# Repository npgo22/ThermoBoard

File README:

STATUS:
Initial decent layout and schematic are complete. PCB meets basic requirements.

TODO:
- Further review

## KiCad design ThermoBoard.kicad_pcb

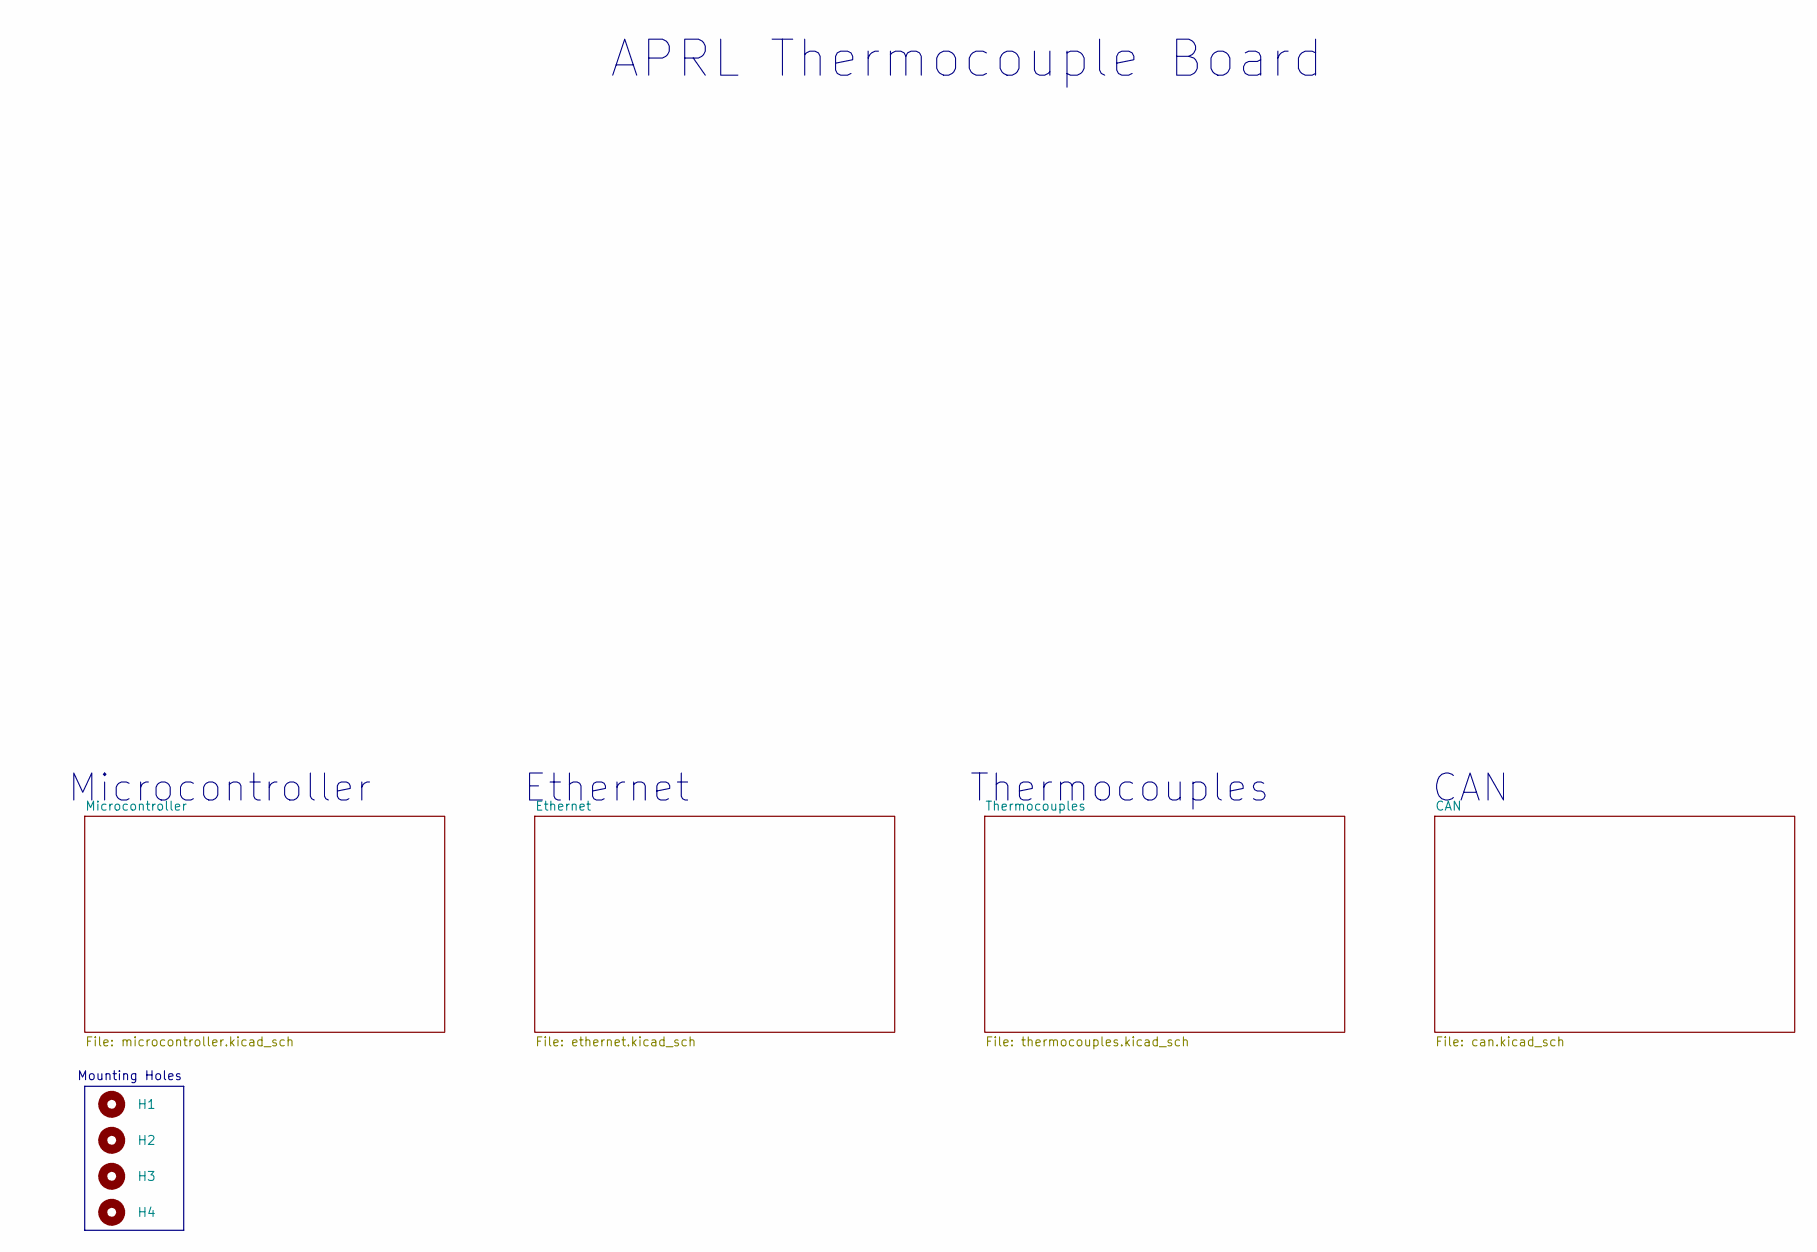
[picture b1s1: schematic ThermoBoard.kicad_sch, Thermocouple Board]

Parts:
H1, H2, H3, H4: MountingHole; MountingHole_3.2mm_M3

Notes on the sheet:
APRL Thermocouple Board
Mounting Holes
Thermocouples
Ethernet
Microcontroller
CAN

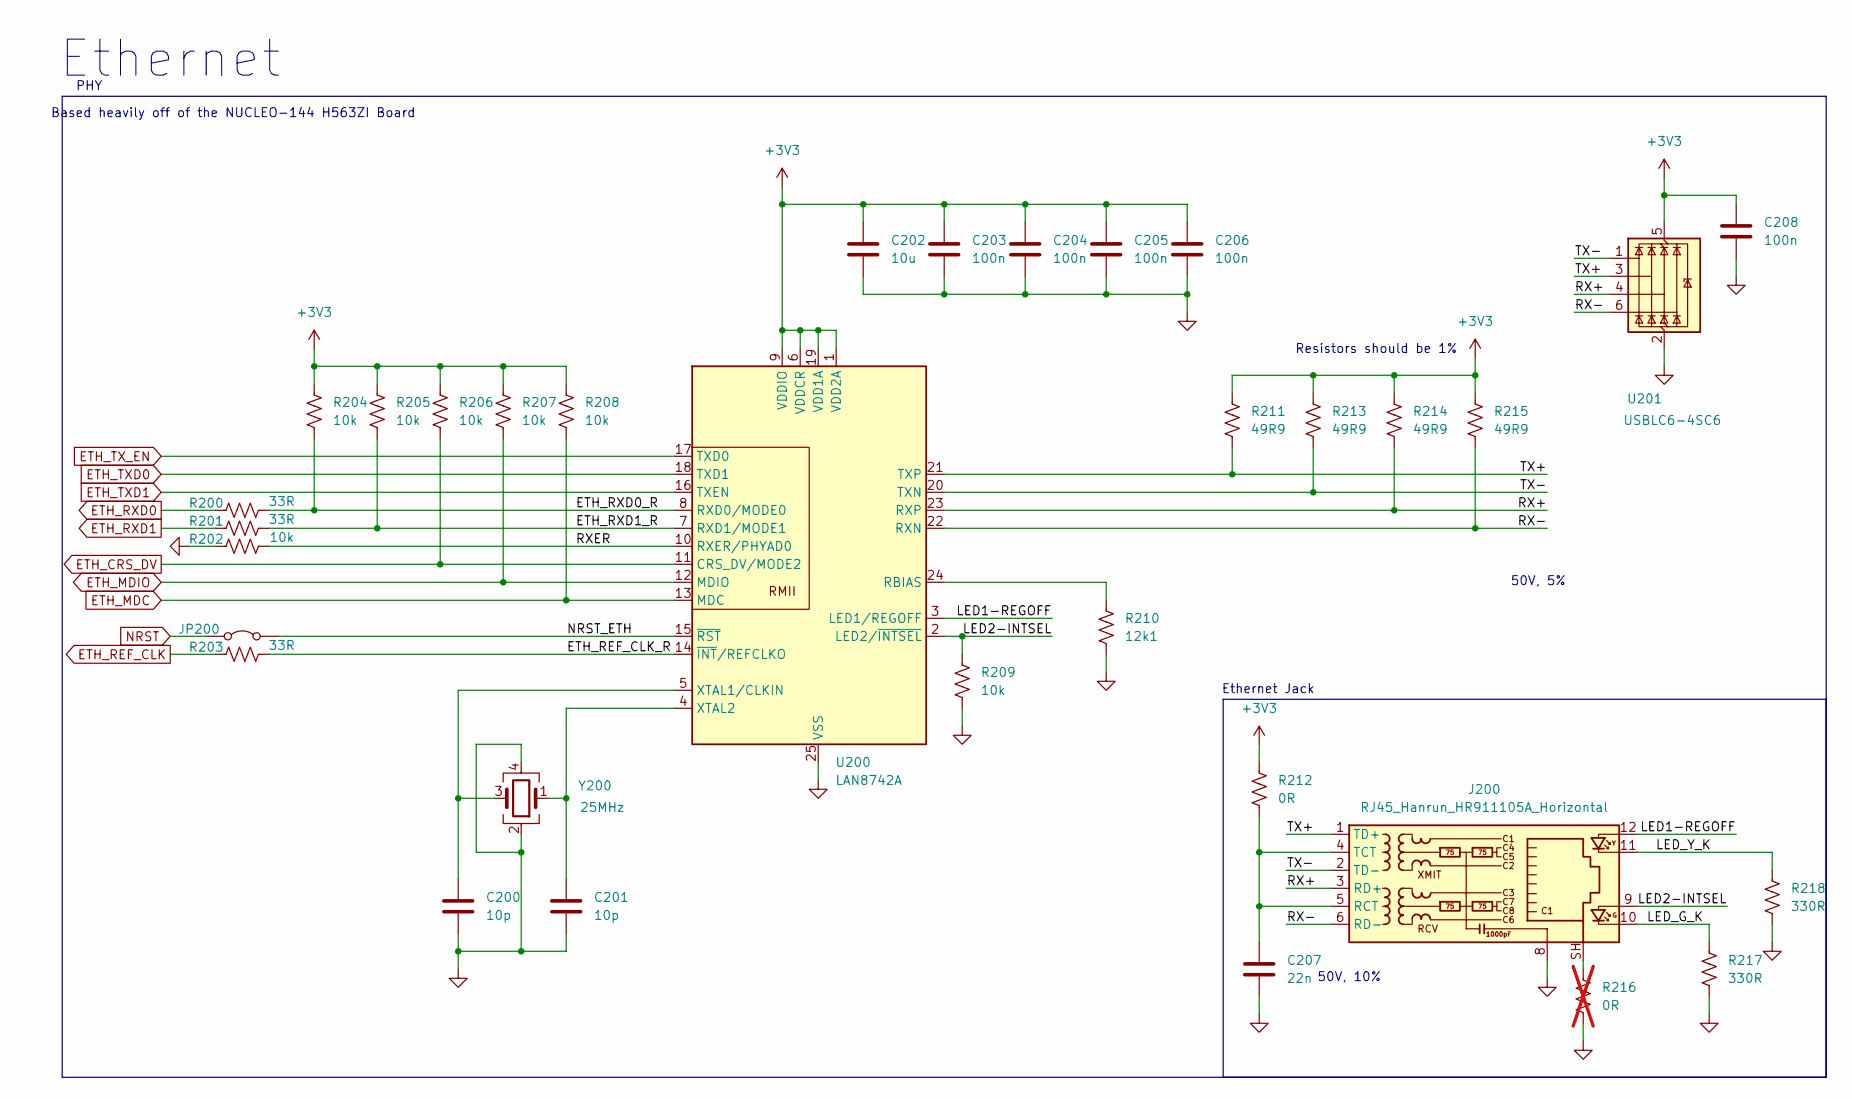
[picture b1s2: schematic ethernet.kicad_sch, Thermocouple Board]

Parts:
C200, C201: 10p; C_0402_1005Metric; LCSC C32949
C202: 10u; C_0603_1608Metric; LCSC C19702
C203, C204, C205, C206, C208: 100n; C_0402_1005Metric; LCSC C1525
C207: 22n; C_0402_1005Metric; LCSC C337699
J200: RJ45_Hanrun_HR911105A_Horizontal; LCSC C12074
JP200: Jumper_2_Bridged; SolderJumper-2_P1.3mm_Bridged_Pad1.0x1.5mm
R200, R201, R203: 33R; R_0402_1005Metric; LCSC C138002
R202, R204, R205, R206, R207, R208, R209: 10k; R_0402_1005Metric; LCSC C60490
R210: 12k1; R_0402_1005Metric; LCSC C25852
R211, R213, R214, R215: 49R9; R_0402_1005Metric; LCSC C87044
R212: 0R; R_0402_1005Metric; LCSC C106231
R216: 0R; R_0402_1005Metric; LCSC C106231; not fitted
R217, R218: 330R; R_0402_1005Metric; LCSC C105875
U200: LAN8742A; VQFN-24-1EP_4x4mm_P0.5mm_EP2.5x2.5mm_ThermalVias; LCSC C220794
U201: USBLC6-4SC6; SOT-23-6; LCSC C111212
Y200: 25MHz; CRYSTAL-SMD_4P-L2.0-W1.6-BL; LCSC C5765970

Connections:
+3V3: C202.1, C203.1, C204.1, C205.1, C206.1, C208.1, R204.1, R205.1, R206.1, R207.1, R208.1, R211.1, R212.1, R213.1, R214.1, R215.1, U200.1 (VDD2A), U200.6 (VDDCR), U200.9 (VDDIO), U200.19 (VDD1A), U201.5 (VBUS); also elsewhere on the board
/Ethernet/ETH_REF_CLK_R: R203.2, U200.14 (~INT/REFCLKO)
/Ethernet/ETH_RXD0_R: R200.2, R204.2, U200.8 (RXD0/MODE0)
/Ethernet/ETH_RXD1_R: R201.2, R205.2, U200.7 (RXD1/MODE1)
/Ethernet/LED1-REGOFF: J200.12, U200.3 (LED1/REGOFF)
/Ethernet/LED2-INTSEL: J200.9, R209.1, U200.2 (LED2/~INTSEL)
/Ethernet/LED_G_K: J200.10, R217.1
/Ethernet/LED_Y_K: J200.11, R218.1
/Ethernet/NRST_ETH: JP200.2 (B), U200.15 (~RST)
/Ethernet/RX+: J200.3 (RD+), R214.2, U200.23 (RXP), U201.4 (I/O3)
/Ethernet/RX-: J200.6 (RD-), R215.2, U200.22 (RXN), U201.6 (I/O4)
/Ethernet/RXER: R202.2, U200.10 (RXER/PHYAD0)
/Ethernet/TX+: J200.1 (TD+), R211.2, U200.21 (TXP), U201.3 (I/O2)
/Ethernet/TX-: J200.2 (TD-), R213.2, U200.20 (TXN), U201.1 (I/O1)
ETH_CRS_DV: R206.2, U200.11 (CRS_DV/MODE2); also elsewhere on the board
ETH_MDC: R208.2, U200.13 (MDC); also elsewhere on the board
ETH_MDIO: R207.2, U200.12 (MDIO); also elsewhere on the board
ETH_REF_CLK: R203.1; also elsewhere on the board
ETH_RXD0: R200.1; also elsewhere on the board
ETH_RXD1: R201.1; also elsewhere on the board
ETH_TXD0: U200.18 (TXD1); also elsewhere on the board
ETH_TXD1: U200.16 (TXEN); also elsewhere on the board
ETH_TX_EN: U200.17 (TXD0); also elsewhere on the board
GND: C200.2, C201.2, C202.2, C203.2, C204.2, C205.2, C206.2, C207.2, C208.2, J200.8, R202.1, R209.2, R210.2, R216.2, R217.2, R218.2, U200.25 (VSS), U201.2 (GND), Y200.2, Y200.4; also elsewhere on the board
NRST: JP200.1 (A); also elsewhere on the board
unnamed: J200.SH, R216.1
unnamed: C207.1, J200.4 (TCT), J200.5 (RCT), R212.2
unnamed: R210.1, U200.24 (RBIAS)
unnamed: C200.1, U200.5 (XTAL1/CLKIN), Y200.3
unnamed: C201.1, U200.4 (XTAL2), Y200.1

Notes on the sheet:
Based heavily off of the NUCLEO-144 H563ZI Board
Ethernet
Resistors should be 1%
Ethernet Jack
PHY
50V, 10%
50V, 5%

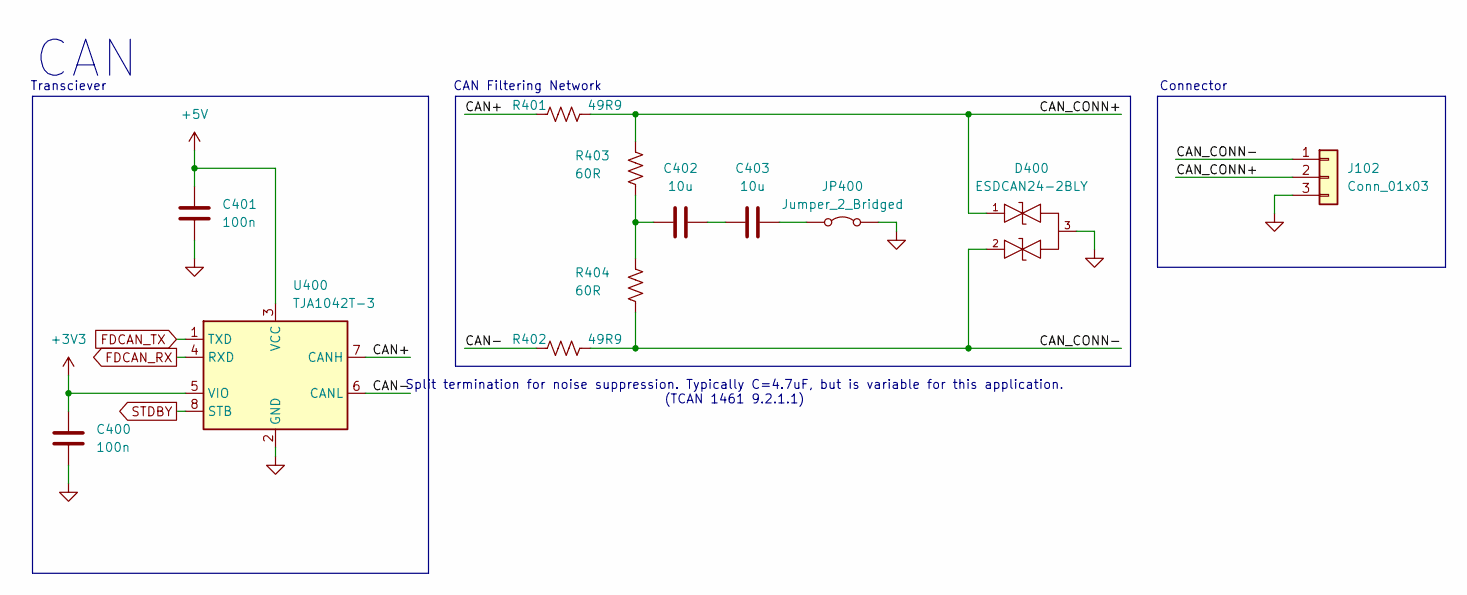
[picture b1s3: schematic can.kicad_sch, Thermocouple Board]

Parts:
C400, C401: 100n; C_0402_1005Metric; LCSC C1525
C402, C403: 10u; C_0603_1608Metric; LCSC C19702
D400: ESDCAN24-2BLY; SOT-23-3; LCSC C246766
J102: Conn_01x03; PinHeader_1x03_P2.54mm_Vertical; LCSC C2337
JP400: Jumper_2_Bridged; PinHeader_1x02_P2.54mm_Vertical; LCSC C2337
R401, R402: 49R9; R_0402_1005Metric; LCSC C87044
R403, R404: 60R; R_0402_1005Metric; LCSC C137954
U400: TJA1042T-3; SOIC-8_3.9x4.9mm_P1.27mm; LCSC C22445414

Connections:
+3V3: C400.1, U400.5 (VIO); also elsewhere on the board
+5V: C401.1, U400.3 (VCC); also elsewhere on the board
/CAN/CAN+: R401.1, U400.7 (CANH)
/CAN/CAN-: R402.1, U400.6 (CANL)
/CAN/CAN_CONN+: D400.1, J102.2, R401.2, R403.1
/CAN/CAN_CONN-: D400.2, J102.1, R402.2, R404.2
FDCAN_RX: U400.4 (RXD); also elsewhere on the board
FDCAN_TX: U400.1 (TXD); also elsewhere on the board
GND: C400.2, C401.2, D400.3, J102.3, JP400.2 (B), U400.2 (GND); also elsewhere on the board
unnamed: C402.1, R403.2, R404.1
unnamed: C402.2, C403.2
unnamed: C403.1, JP400.1 (A)
STDBY: U400.8 (STB); also elsewhere on the board

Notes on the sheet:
Split termination for noise suppression. Typically C=4.7uF, but is variable for this application. (TCAN 1461 9.2.1.1)
CAN
Transciever
CAN Filtering Network
Connector

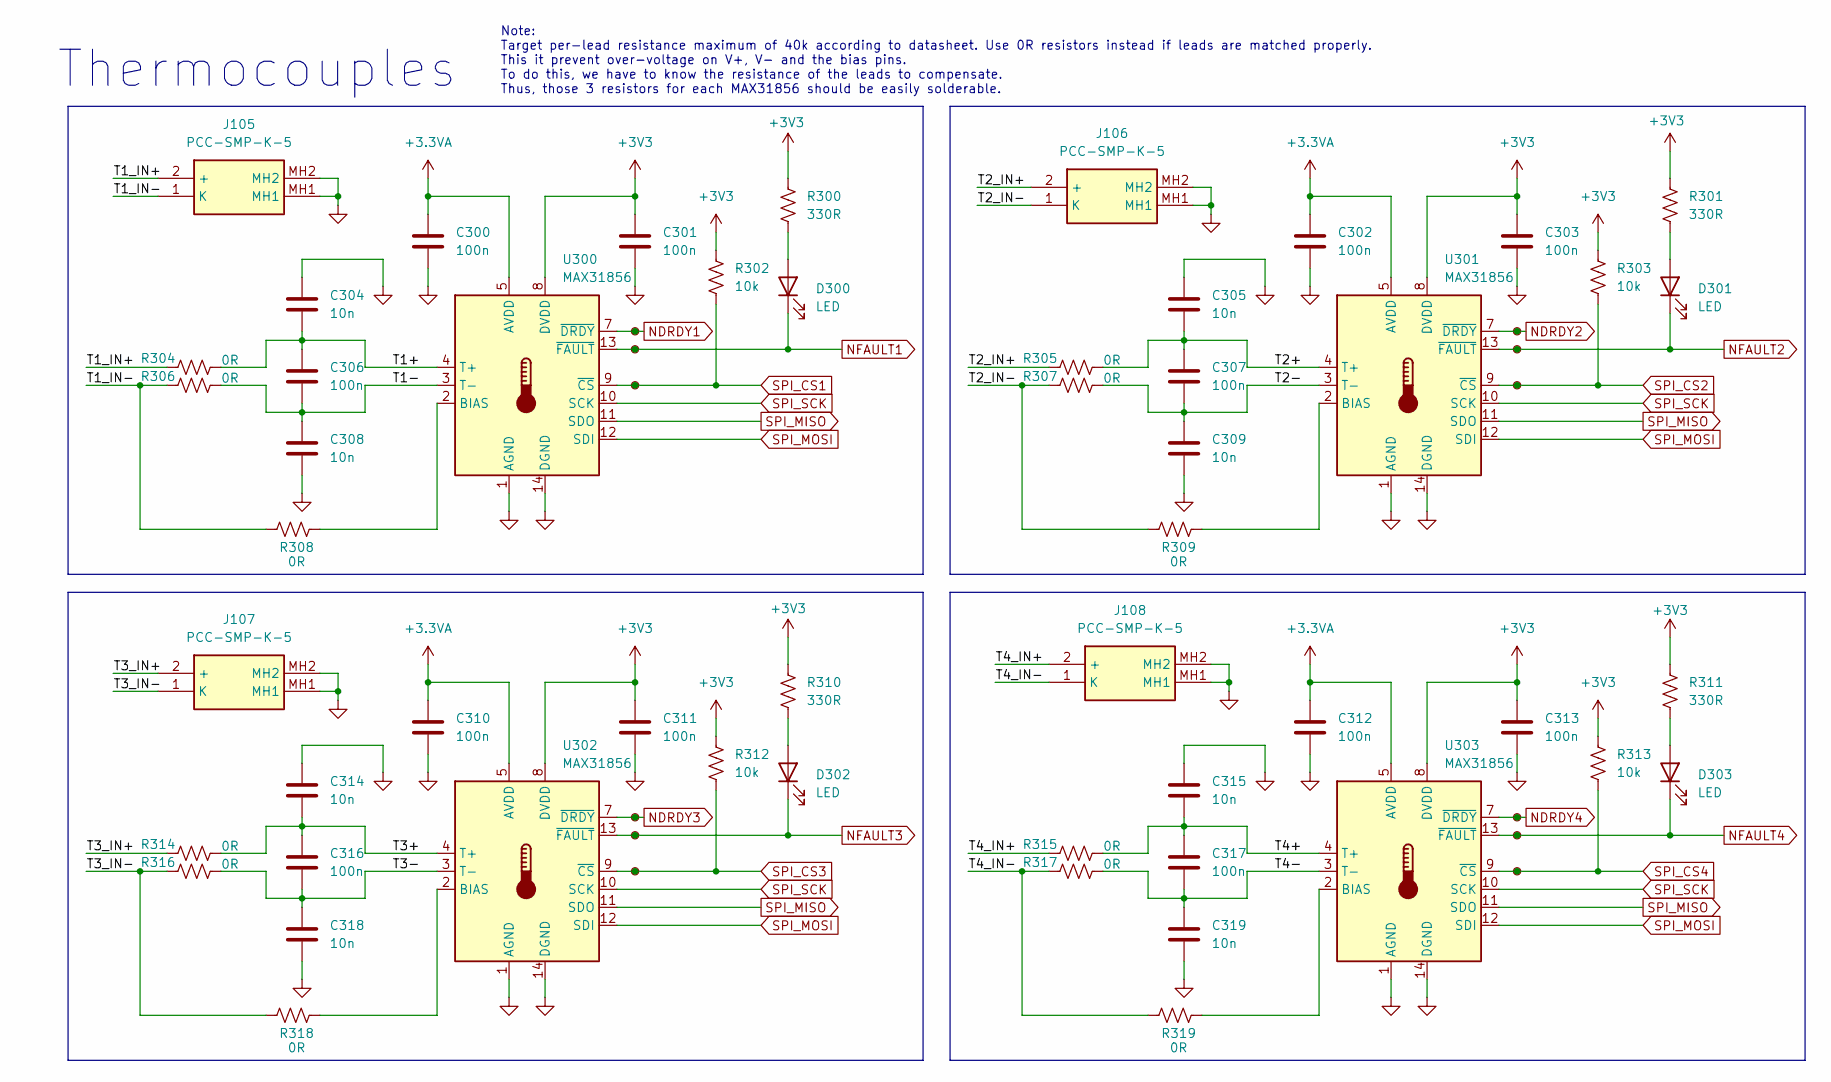
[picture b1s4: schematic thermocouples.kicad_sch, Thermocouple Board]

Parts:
C300, C301, C302, C303, C306, C307, C310, C311, C312, C313, C316, C317: 100n; C_0402_1005Metric; LCSC C1525
C304, C305, C308, C309, C314, C315, C318, C319: 10n; C_0402_1005Metric; LCSC C15195
D300, D301, D302, D303: LED; LED_0402_1005Metric; LCSC C965793
J105, J106, J107, J108: PCC-SMP-K-5; PCCSMPK5; Manufacturer_Part_Number PCC-SMP-K-5
R300, R301, R310, R311: 330R; R_0402_1005Metric; LCSC C105875
R302, R303, R312, R313: 10k; R_0402_1005Metric; LCSC C60490
R304, R305, R306, R307, R308, R309, R314, R315, R316, R317, R318, R319: 0R; R_0603_1608Metric; LCSC C95177
TP106, TP107, TP108, TP109, TP110, TP114, TP115, TP116, TP120, TP121, TP122, TP300: TestPoint_Small; TestPoint_Pad_D1.0mm
U300, U301, U302, U303: MAX31856; TSSOP-14_4.4x5mm_P0.65mm; LCSC C2653162

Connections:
+3.3VA: C300.1, C302.1, C310.1, C312.1, U300.5 (AVDD), U301.5 (AVDD), U302.5 (AVDD), U303.5 (AVDD); also elsewhere on the board
+3V3: C301.1, C303.1, C311.1, C313.1, R300.1, R301.1, R302.1, R303.1, R310.1, R311.1, R312.1, R313.1, U300.8 (DVDD), U301.8 (DVDD), U302.8 (DVDD), U303.8 (DVDD); also elsewhere on the board
/Thermocouples/T1+: C304.2, C306.1, R304.2, U300.4 (T+)
/Thermocouples/T1-: C306.2, C308.1, R306.2, U300.3 (T-)
/Thermocouples/T1_IN+: J105.2 (+), R304.1
/Thermocouples/T1_IN-: J105.1 (K), R306.1, R308.1
/Thermocouples/T2+: C305.2, C307.1, R305.2, U301.4 (T+)
/Thermocouples/T2-: C307.2, C309.1, R307.2, U301.3 (T-)
/Thermocouples/T2_IN+: J106.2 (+), R305.1
/Thermocouples/T2_IN-: J106.1 (K), R307.1, R309.1
/Thermocouples/T3+: C314.2, C316.1, R314.2, U302.4 (T+)
/Thermocouples/T3-: C316.2, C318.1, R316.2, U302.3 (T-)
/Thermocouples/T3_IN+: J107.2 (+), R314.1
/Thermocouples/T3_IN-: J107.1 (K), R316.1, R318.1
/Thermocouples/T4+: C315.2, C317.1, R315.2, U303.4 (T+)
/Thermocouples/T4-: C317.2, C319.1, R317.2, U303.3 (T-)
/Thermocouples/T4_IN+: J108.2 (+), R315.1
/Thermocouples/T4_IN-: J108.1 (K), R317.1, R319.1
GND: C300.2, C301.2, C302.2, C303.2, C304.1, C305.1, C308.2, C309.2, C310.2, C311.2, C312.2, C313.2, C314.1, C315.1, C318.2, C319.2, J105.MH1, J105.MH2, J106.MH1, J106.MH2, J107.MH1, J107.MH2, J108.MH1, J108.MH2, U300.1 (AGND), U300.14 (DGND), U301.1 (AGND), U301.14 (DGND), U302.1 (AGND), U302.14 (DGND), U303.1 (AGND), U303.14 (DGND); also elsewhere on the board
NDRDY1: TP106.1, U300.7 (~DRDY); also elsewhere on the board
NDRDY2: TP114.1, U301.7 (~DRDY); also elsewhere on the board
NDRDY3: TP108.1, U302.7 (~DRDY); also elsewhere on the board
NDRDY4: TP120.1, U303.7 (~DRDY); also elsewhere on the board
NFAULT1: D300.1 (K), TP107.1, U300.13 (~FAULT); also elsewhere on the board
NFAULT2: D301.1 (K), TP115.1, U301.13 (~FAULT); also elsewhere on the board
NFAULT3: D302.1 (K), TP109.1, U302.13 (~FAULT); also elsewhere on the board
NFAULT4: D303.1 (K), TP121.1, U303.13 (~FAULT); also elsewhere on the board
unnamed: D300.2 (A), R300.2
unnamed: D301.2 (A), R301.2
unnamed: D302.2 (A), R310.2
unnamed: D303.2 (A), R311.2
unnamed: R308.2, U300.2 (BIAS)
unnamed: R309.2, U301.2 (BIAS)
unnamed: R318.2, U302.2 (BIAS)
unnamed: R319.2, U303.2 (BIAS)
SPI_CS1: R302.2, TP300.1, U300.9 (~CS); also elsewhere on the board
SPI_CS2: R303.2, TP116.1, U301.9 (~CS); also elsewhere on the board
SPI_CS3: R312.2, TP110.1, U302.9 (~CS); also elsewhere on the board
SPI_CS4: R313.2, TP122.1, U303.9 (~CS); also elsewhere on the board
SPI_MISO: U300.11 (SDO), U301.11 (SDO), U302.11 (SDO), U303.11 (SDO); also elsewhere on the board
SPI_MOSI: U300.12 (SDI), U301.12 (SDI), U302.12 (SDI), U303.12 (SDI); also elsewhere on the board
SPI_SCK: U300.10 (SCK), U301.10 (SCK), U302.10 (SCK), U303.10 (SCK); also elsewhere on the board

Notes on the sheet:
Note: Target per-lead resistance maximum of 40k according to datasheet. Use 0R resistors instead if leads are matched properly. This it prevent over-voltage on V+, V- and the bias pins. To do this, we have to know the resistance of the leads to compensate. Thus, those 3 resistors for each MAX31856 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
Thermocouples

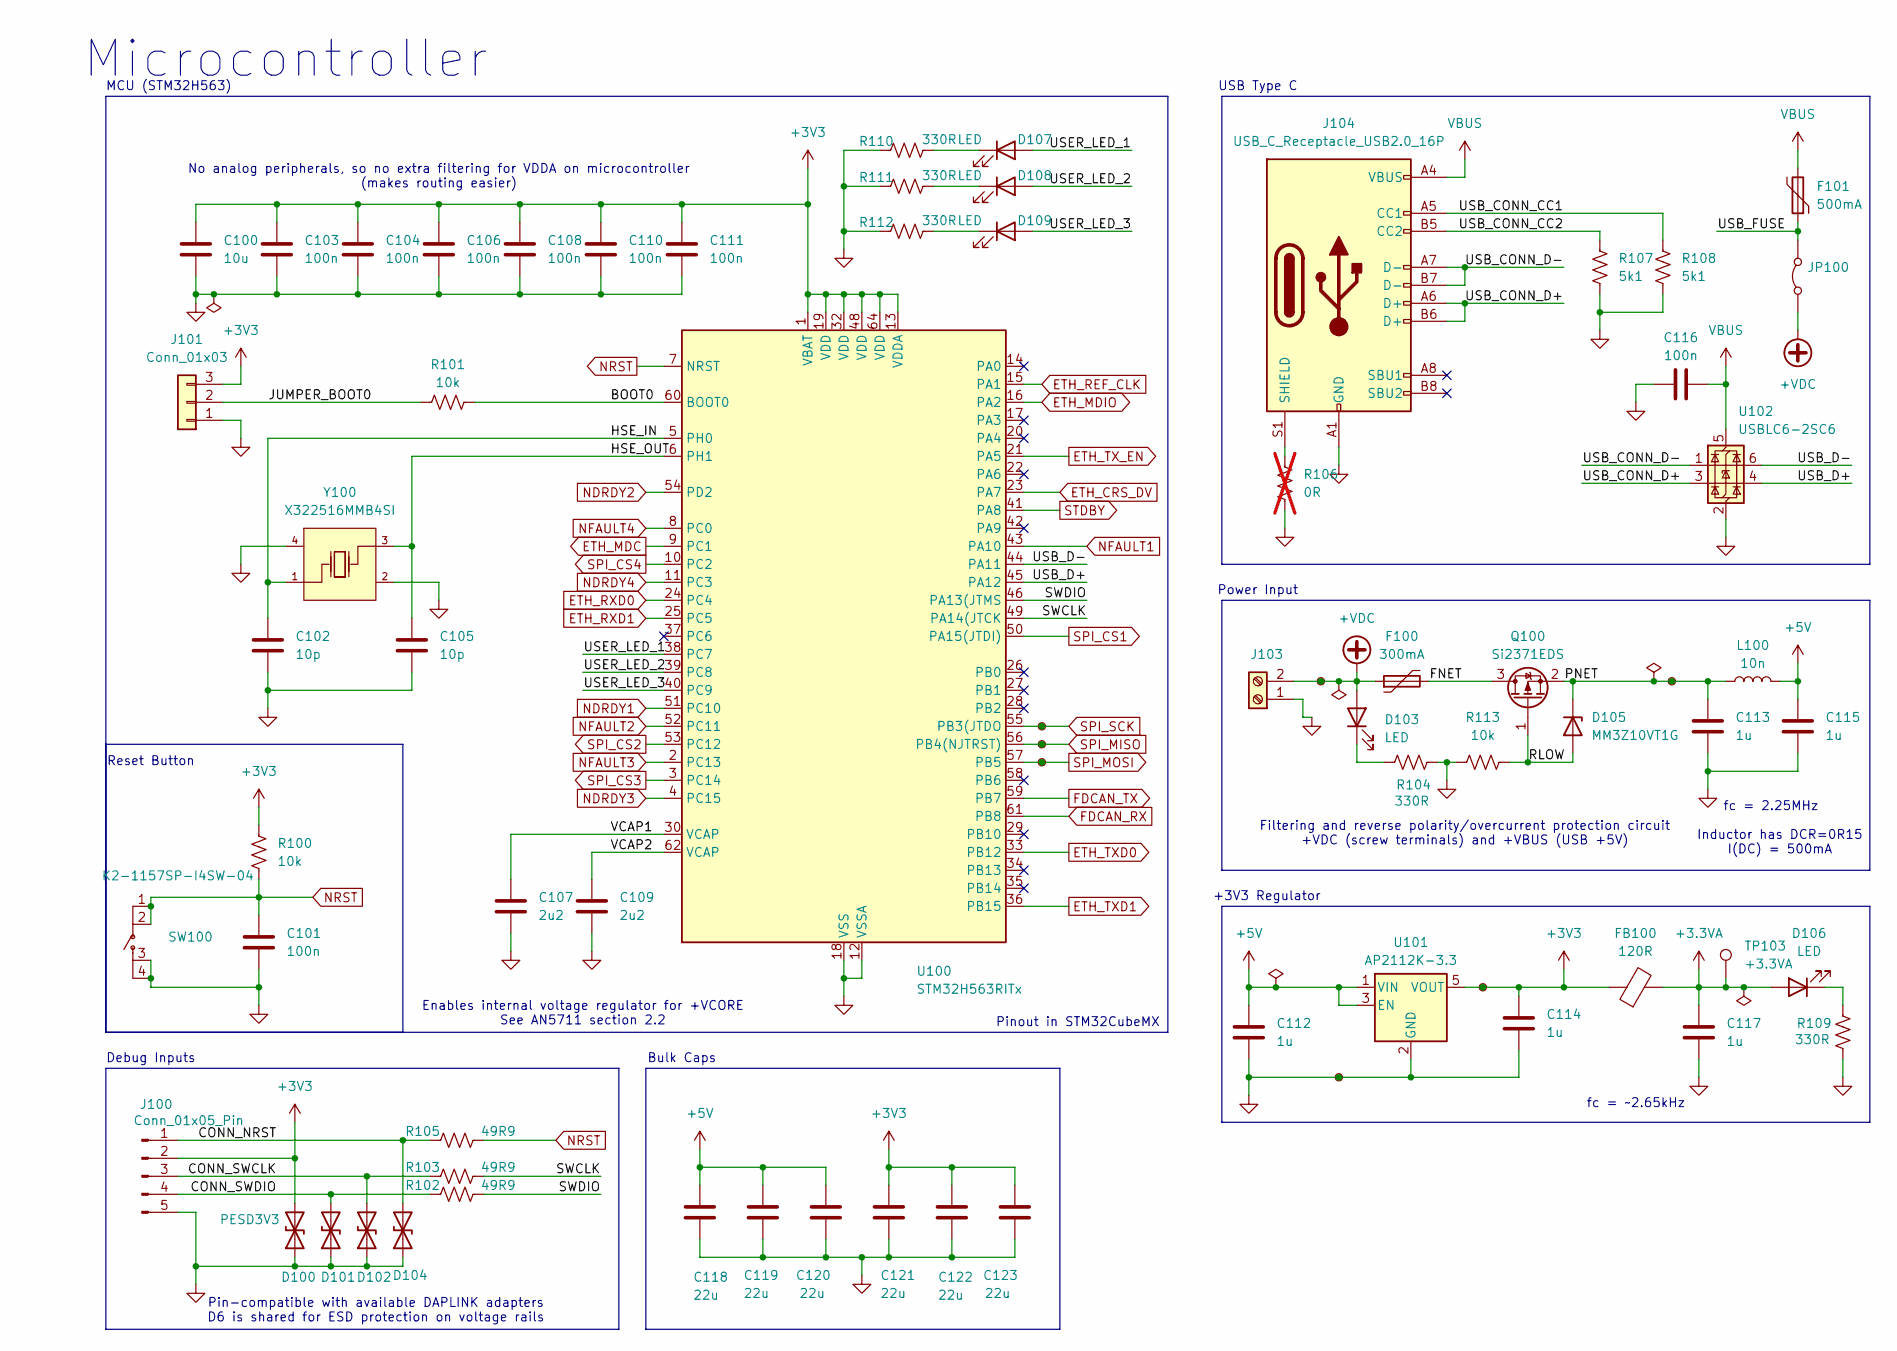
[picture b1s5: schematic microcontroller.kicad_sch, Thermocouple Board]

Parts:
C100: 10u; C_0603_1608Metric; LCSC C19702
C101, C103, C104, C106, C108, C110, C111, C116: 100n; C_0402_1005Metric; LCSC C1525
C102, C105: 10p; C_0402_1005Metric; LCSC C32949
C107, C109: 2u2; C_0402_1005Metric; LCSC C170151
C112, C113, C114, C115, C117: 1u; C_0603_1608Metric; LCSC C15849
C118, C119, C120, C121, C122, C123: 22u; C_0805_2012Metric; LCSC C602037
D100, D101, D102, D104: PESD3V3; D_SOD-323; LCSC C51450
D103, D106, D107, D108, D109: LED; LED_0402_1005Metric; LCSC C965793
D105: MM3Z10VT1G; D_SOD-323; LCSC C39057
F100: 300mA; C_0603_1608Metric; LCSC C19193027
F101: 500mA; C_0603_1608Metric; LCSC C883095
FB100: 120R; C_0603_1608Metric; LCSC C41330
J100: Conn_01x05_Pin; PinHeader_1x05_P2.54mm_Vertical; LCSC C2337
J101: Conn_01x03; PinHeader_1x03_P2.54mm_Vertical; LCSC C2337
J103: Screw_Terminal_01x02; TerminalBlock_Phoenix_MPT-0,5-2-2.54_1x02_P2.54mm_Horizontal; LCSC C3029316
J104: USB_C_Receptacle_USB2.0_16P; USB_C_Receptacle_HRO_TYPE-C-31-M-12; LCSC C165948
JP100: Jumper_2_Bridged; PinHeader_1x02_P2.54mm_Vertical; LCSC C2337
L100: 10n; L_0603_1608Metric; LCSC C1589
Q100: Si2371EDS; SOT-23; LCSC C467897
R100, R101, R113: 10k; R_0402_1005Metric; LCSC C60490
R102, R103, R105: 49R9; R_0402_1005Metric; LCSC C87044
R104, R109, R110, R111, R112: 330R; R_0402_1005Metric; LCSC C105875
R106: 0R; R_0402_1005Metric; LCSC C106231; not fitted
R107, R108: 5k1; R_0402_1005Metric; LCSC C105873
SW100: K2-1157SP-I4SW-04; SW-SMD_4P-L6.2-W6.2-P4.50-LS8.6; LCSC C2909692
TP100, TP101, TP102, TP104, TP105, TP111, TP112: TestPoint_Small; TestPoint_Pad_D1.0mm
TP103: +3.3VA; TestPoint_Pad_D1.5mm
U100: STM32H563RITx; LQFP-64_10x10mm_P0.5mm; LCSC C20619634
U101: AP2112K-3.3; SOT-23-5; LCSC C51118
U102: USBLC6-2SC6; SOT-23-6; LCSC C7519
Y100: X322516MMB4SI; CRYSTAL-SMD_4P-L2.0-W1.6-BL; LCSC C112972

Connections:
+3.3VA: C117.1, D106.2 (A), FB100.2, TP103.1; also elsewhere on the board
+3V3: C100.1, C103.1, C104.1, C106.1, C108.1, C110.1, C111.1, C114.1, C121.2, C122.2, C123.2, D100.2 (A2), FB100.1, J100.2, J101.3, R100.1, TP102.1, U100.1 (VBAT), U100.13 (VDDA), U100.19 (VDD), U100.32 (VDD), U100.48 (VDD), U100.64 (VDD), U101.5 (VOUT); also elsewhere on the board
+5V: C112.1, C115.1, C118.2, C119.2, C120.2, L100.2, U101.1 (VIN), U101.3 (EN); also elsewhere on the board
+VDC: D103.2 (A), F100.1, J103.2, JP100.1 (A), TP101.1
/Microcontroller/BOOT0: R101.2, U100.60 (BOOT0)
/Microcontroller/CONN_NRST: D104.2 (A2), J100.1, R105.1
/Microcontroller/CONN_SWCLK: D102.2 (A2), J100.3, R103.1
/Microcontroller/CONN_SWDIO: D101.2 (A2), J100.4, R102.1
/Microcontroller/FNET: F100.2, Q100.3 (D)
/Microcontroller/HSE_IN: C102.1, U100.5 (PH0), Y100.1
/Microcontroller/HSE_OUT: C105.1, U100.6 (PH1), Y100.3
/Microcontroller/JUMPER_BOOT0: J101.2, R101.1
/Microcontroller/PNET: C113.1, D105.1 (K), L100.1, Q100.2 (S), TP111.1
/Microcontroller/RLOW: D105.2 (A), Q100.1 (G), R113.2
/Microcontroller/SWCLK: R103.2, U100.49 (PA14(JTCK)
/Microcontroller/SWDIO: R102.2, U100.46 (PA13(JTMS)
/Microcontroller/USB_CONN_CC1: J104.A5 (CC1), R108.1
/Microcontroller/USB_CONN_CC2: J104.B5 (CC2), R107.1
/Microcontroller/USB_CONN_D+: J104.A6 (D+), J104.B6 (D+), U102.3 (I/O2)
/Microcontroller/USB_CONN_D-: J104.A7 (D-), J104.B7 (D-), U102.1 (I/O1)
/Microcontroller/USB_D+: U100.45 (PA12), U102.4 (I/O2)
/Microcontroller/USB_D-: U100.44 (PA11), U102.6 (I/O1)
/Microcontroller/USB_FUSE: F101.1, JP100.2 (B)
/Microcontroller/USER_LED_1: D107.2 (A), U100.38 (PC7)
/Microcontroller/USER_LED_2: D108.2 (A), U100.39 (PC8)
/Microcontroller/USER_LED_3: D109.2 (A), U100.40 (PC9)
/Microcontroller/VCAP1: C107.1, U100.30 (VCAP)
/Microcontroller/VCAP2: C109.1, U100.62 (VCAP)
ETH_CRS_DV: U100.23 (PA7); also elsewhere on the board
ETH_MDC: U100.9 (PC1); also elsewhere on the board
ETH_MDIO: U100.16 (PA2); also elsewhere on the board
ETH_REF_CLK: U100.15 (PA1); also elsewhere on the board
ETH_RXD0: U100.24 (PC4); also elsewhere on the board
ETH_RXD1: U100.25 (PC5); also elsewhere on the board
ETH_TXD0: U100.33 (PB12); also elsewhere on the board
ETH_TXD1: U100.36 (PB15); also elsewhere on the board
ETH_TX_EN: U100.21 (PA5); also elsewhere on the board
FDCAN_RX: U100.61 (PB8); also elsewhere on the board
FDCAN_TX: U100.59 (PB7); also elsewhere on the board
GND: C100.2, C101.2, C102.2, C103.2, C104.2, C105.2, C106.2, C107.2, C108.2, C109.2, C110.2, C111.2, C112.2, C113.2, C114.2, C115.2, C116.1, C117.2, C118.1, C119.1, C120.1, C121.1, C122.1, C123.1, D100.1 (A1), D101.1 (A1), D102.1 (A1), D104.1 (A1), J100.5, J101.1, J103.1, J104.A1 (GND), J104.A12 (GND), J104.B1 (GND), J104.B12 (GND), R104.2, R106.2, R107.2, R108.2, R109.2, R110.1, R111.1, R112.1, R113.1, SW100.3, SW100.4, TP112.1, U100.12 (VSSA), U100.18 (VSS), U100.31 (VSS), U100.47 (VSS), U100.63 (VSS), U101.2 (GND), U102.2 (GND), Y100.2, Y100.4; also elsewhere on the board
NDRDY1: U100.51 (PC10); also elsewhere on the board
NDRDY2: U100.54 (PD2); also elsewhere on the board
NDRDY3: U100.4 (PC15); also elsewhere on the board
NDRDY4: U100.11 (PC3); also elsewhere on the board
NFAULT1: U100.43 (PA10); also elsewhere on the board
NFAULT2: U100.52 (PC11); also elsewhere on the board
NFAULT3: U100.2 (PC13); also elsewhere on the board
NFAULT4: U100.8 (PC0); also elsewhere on the board
NRST: C101.1, R100.2, R105.2, SW100.1, SW100.2, U100.7 (NRST); also elsewhere on the board
unnamed: D103.1 (K), R104.1
unnamed: D106.1 (K), R109.1
unnamed: D107.1 (K), R110.2
unnamed: D108.1 (K), R111.2
unnamed: D109.1 (K), R112.2
unnamed: J104.S1 (SHIELD), R106.1
SPI_CS1: U100.50 (PA15(JTDI)); also elsewhere on the board
SPI_CS2: U100.53 (PC12); also elsewhere on the board
SPI_CS3: U100.3 (PC14); also elsewhere on the board
SPI_CS4: U100.10 (PC2); also elsewhere on the board
SPI_MISO: TP104.1, U100.56 (PB4(NJTRST)); also elsewhere on the board
SPI_MOSI: TP105.1, U100.57 (PB5); also elsewhere on the board
SPI_SCK: TP100.1, U100.55 (PB3(JTDO); also elsewhere on the board
STDBY: U100.41 (PA8); also elsewhere on the board
VBUS: C116.2, F101.2, J104.A4 (VBUS), J104.A9 (VBUS), J104.B4 (VBUS), J104.B9 (VBUS), U102.5 (VBUS)

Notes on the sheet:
fc = 2.25MHz
Microcontroller
Reset Button
Debug Inputs
Power Input
fc = ~2.65kHz
Inductor has DCR=0R15 I(DC) = 500mA
+3V3 Regulator
Pinout in STM32CubeMX
Pin-compatible with available DAPLINK adapters D6 is shared for ESD protection on voltage rails
Enables internal voltage regulator for +VCORE See AN5711 section 2.2
No analog peripherals, so no extra filtering for VDDA on microcontroller (makes routing easier)
Bulk Caps
Filtering and reverse polarity/overcurrent protection circuit +VDC (screw terminals) and +VBUS (USB +5V)
USB Type C
MCU (STM32H563)

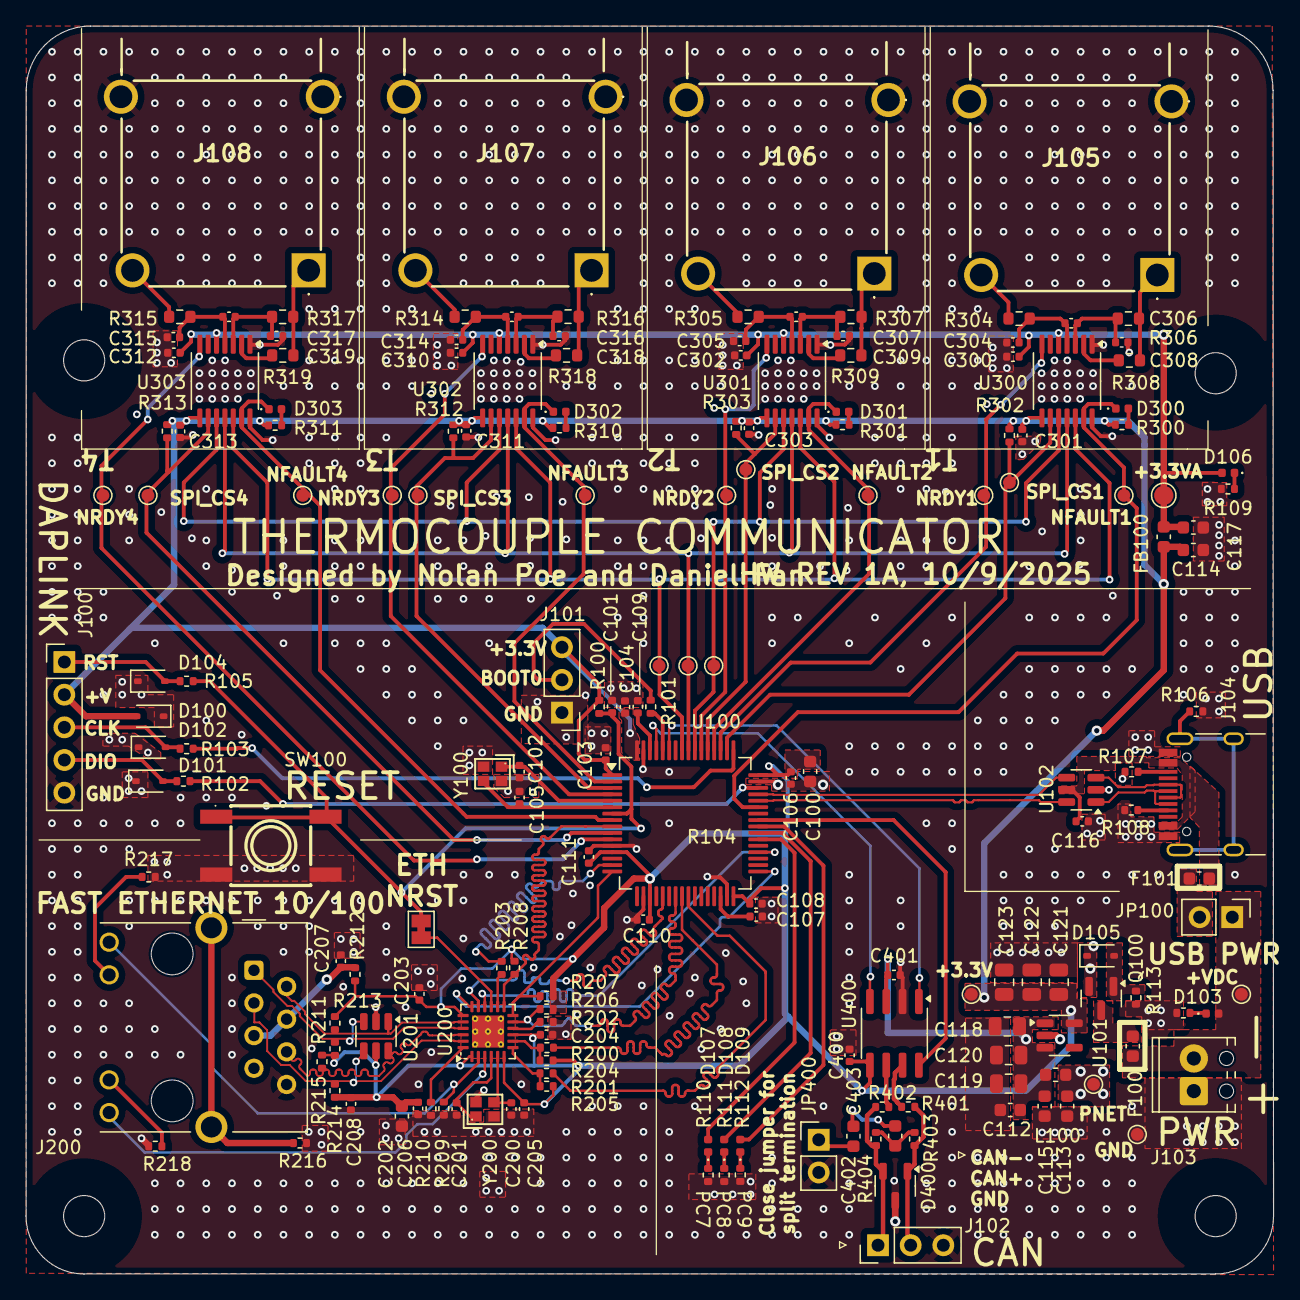
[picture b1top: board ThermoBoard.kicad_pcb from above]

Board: 4 copper layers, 97.0 x 97.0 mm, 184 parts (0 on the bottom side), 113 nets.

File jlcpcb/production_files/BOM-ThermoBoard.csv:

Comment,Designator,Footprint,LCSC,Quantity
0R,R212,R_0402_1005Metric,C106231,1
0R,"R304,R305,R306,R307,R308,R309,R314,R315,R316,R317,R318,R319",R_0603_1608Metric,C95177,12
100n,"C101,C103,C104,C106,C108,C110,C111,C116,C203,C204,C205,C206,C208,C300,C301,C302,C303,C306,C307,C310,C311,C312,C313,C316,C317,C400,C401",C_0402_1005Metric,C1525,27
10k,"R100,R101,R202,R204,R205,R206,R207,R208,R209,R302,R303,R312,R313",R_0402_1005Metric,C60490,13
10n,"C304,C305,C308,C309,C314,C315,C318,C319",C_0402_1005Metric,C15195,8
10n,L100,L_0603_1608Metric,C1589,1
10p,"C102,C105,C200,C201",C_0402_1005Metric,C32949,4
10u,"C100,C202,C402,C403",C_0603_1608Metric,C19702,4
120R,FB100,C_0603_1608Metric,C41330,1
12k1,R210,R_0402_1005Metric,C25852,1
1u,"C112,C113,C114,C115,C117",C_0603_1608Metric,C15849,5
22n,C207,C_0402_1005Metric,C337699,1
22u,"C118,C119,C120,C121,C122,C123",C_0805_2012Metric,C602037,6
25MHz,Y200,CRYSTAL-SMD_4P-L2.0-W1.6-BL,C5765970,1
2u2,"C107,C109",C_0402_1005Metric,C170151,2
300mA,F100,C_0603_1608Metric,C19193027,1
330R,"R104,R109,R110,R111,R112,R217,R218,R300,R301,R310,R311",R_0402_1005Metric,C105875,11
33R,"R200,R201,R203",R_0402_1005Metric,C138002,3
49R9,"R102,R103,R105,R211,R213,R214,R215,R401,R402",R_0402_1005Metric,C87044,9
500mA,F101,C_0603_1608Metric,C883095,1
5k1,"R107,R108",R_0402_1005Metric,C105873,2
60R,"R403,R404",R_0402_1005Metric,C137954,2
AP2112K-3.3,U101,SOT-23-5,C51118,1
Conn_01x03,"J101,J102",PinHeader_1x03_P2.54mm_Vertical,C2337,2
Conn_01x05_Pin,J100,PinHeader_1x05_P2.54mm_Vertical,C2337,1
ESDCAN24-2BLY,D400,SOT-23-3,C246766,1
Jumper_2_Bridged,"JP100,JP400",PinHeader_1x02_P2.54mm_Vertical,C2337,2
K2-1157SP-I4SW-04,SW100,SW-SMD_4P-L6.2-W6.2-P4.50-LS8.6,C2909692,1
LAN8742A,U200,VQFN-24-1EP_4x4mm_P0.5mm_EP2.5x2.5mm_ThermalVias,C220794,1
LED,"D103,D106,D107,D108,D109,D300,D301,D302,D303",LED_0402_1005Metric,C965793,9
MAX31856,"U300,U301,U302,U303",TSSOP-14_4.4x5mm_P0.65mm,C2653162,4
PESD3V3,"D100,D101,D102,D104",D_SOD-323,C51450,4
RJ45_Hanrun_HR911105A_Horizontal,J200,RJ45_Hanrun_HR911105A_Horizontal,C12074,1
STM32H563RITx,U100,LQFP-64_10x10mm_P0.5mm,C20619634,1
Screw_Terminal_01x02,J103,"TerminalBlock_Phoenix_MPT-0,5-2-2.54_1x02_P2.54mm_Horizontal",C3029316,1
TJA1042T-3,U400,SOIC-8_3.9x4.9mm_P1.27mm,C22445414,1
USBLC6-2SC6,U102,SOT-23-6,C7519,1
USBLC6-4SC6,U201,SOT-23-6,C111212,1
USB_C_Receptacle_USB2.0_16P,J104,USB_C_Receptacle_HRO_TYPE-C-31-M-12,C165948,1
X322516MMB4SI,Y100,CRYSTAL-SMD_4P-L2.0-W1.6-BL,C112972,1
PCC-SMP-K-5,J108,PCCSMPK5,,1
PCC-SMP-K-5,J107,PCCSMPK5,,1
PCC-SMP-K-5,J106,PCCSMPK5,,1
PCC-SMP-K-5,J105,PCCSMPK5,,1
+3.3VA,TP103,TestPoint_Pad_D1.5mm,,1
1N4148WT,D105,D_SOD-523,,1

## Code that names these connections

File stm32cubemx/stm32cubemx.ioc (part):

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Mcu.Name=STM32H563RITx
Mcu.Package=LQFP64
Mcu.UserName=STM32H563RITx
PA1.Mode=RMII
PA1.Signal=ETH_REF_CLK
PA10.Signal=GPIO_Input
PA11.Mode=Device
PA11.Signal=USB_DM
PA12.Mode=Device
PA12.Signal=USB_DP
PA13(JTMS/SWDIO).Signal=DEBUG_JTMS-SWDIO
PA14(JTCK/SWCLK).Signal=DEBUG_JTCK-SWCLK
PA15(JTDI).Signal=GPIO_Output
PA2.Mode=RMII
PA2.Signal=ETH_MDIO
PA5.Mode=RMII
PA5.Signal=ETH_TX_EN
PA7.Mode=RMII
PA7.Signal=ETH_CRS_DV
PA8.Signal=GPIO_Output
PB12.Mode=RMII
PB12.Signal=ETH_TXD0
PB15.Mode=RMII
PB15.Signal=ETH_TXD1
PB3(JTDO/TRACESWO).Mode=Full_Duplex_Master
PB3(JTDO/TRACESWO).Signal=SPI1_SCK
PB4(NJTRST).Mode=Full_Duplex_Master
PB4(NJTRST).Signal=SPI1_MISO
PB5.Mode=Full_Duplex_Master
PB5.Signal=SPI1_MOSI
PB7.Mode=FDCAN_Activate
PB7.Signal=FDCAN1_TX
PB8.Mode=FDCAN_Activate
PB8.Signal=FDCAN1_RX
PC0.Signal=GPIO_Input
PC1.Mode=RMII
PC1.Signal=ETH_MDC
PC10.Signal=GPIO_Input
PC11.Signal=GPIO_Input
PC12.Signal=GPIO_Output
PC13.Signal=GPIO_Input
PC14-OSC32_IN(OSC32_IN).Signal=GPIO_Output
PC15-OSC32_OUT(OSC32_OUT).Signal=GPIO_Input
PC2.Signal=GPIO_Output
PC3.Signal=GPIO_Input
PC4.Mode=RMII
PC4.Signal=ETH_RXD0
PC5.Mode=RMII
PC5.Signal=ETH_RXD1
PC7.Signal=GPIO_Output
PC8.Signal=GPIO_Output
PC9.Signal=GPIO_Output
PD2.Signal=GPIO_Input
PH0-OSC_IN(PH0).Mode=HSE-External-Oscillator
PH0-OSC_IN(PH0).Signal=RCC_OSC_IN
PH1-OSC_OUT(PH1).Mode=HSE-External-Oscillator
PH1-OSC_OUT(PH1).Signal=RCC_OSC_OUT
RCC.HSE_VALUE=25000000
RCC.SYSCLKFreq_VALUE=32000000
board=custom

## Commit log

2025-10-07 Add schematic
2025-10-07 Add README
2025-10-07 A4 -> USLetter sheets
2025-10-08 Footprints added
2025-10-08 Some changes to power circuitry, more layout
2025-10-08 Some more schematic updates
2025-10-08 Extremely incomplete, preliminary, pre-alpha, ugly layout
2025-10-08 First decent layout
2025-10-08 Better plots, make the fuse really obvious
2025-10-08 Pre-via
2025-10-08 Actually Pre-via
2025-10-08 Post-stitch
2025-10-08 Regenerate output files
2025-10-09 I hate everything
2025-10-09 First workable layout
2025-10-09 Added pfet for reverse polarity protection, moved power circuitry away from analog parts
2025-10-10 Apply Daniel's suggestions
2025-10-10 Modify repo for usage on Linux, add basic CI
    chore: fix CI
    Small things
2025-10-10 Silkscreen stuff
2025-10-10 Swap to ESD204 for ethernet to enable better routing
2025-10-10 Minor updates
2025-10-10 chore: Minor changes
2025-10-10 Fix major ethernet silkscreen placement and re-add DRC rules
